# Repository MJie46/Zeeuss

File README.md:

# Zeeuss
>

#### IP5306+MP2045,电池充放电管理和升压输出
#### 背面引出5v,3.3v,BATT,VBUS,GND

###2.0版本
#### 尺寸 2.5x14mm

###1.0版本
#### 尺寸 20x18mm

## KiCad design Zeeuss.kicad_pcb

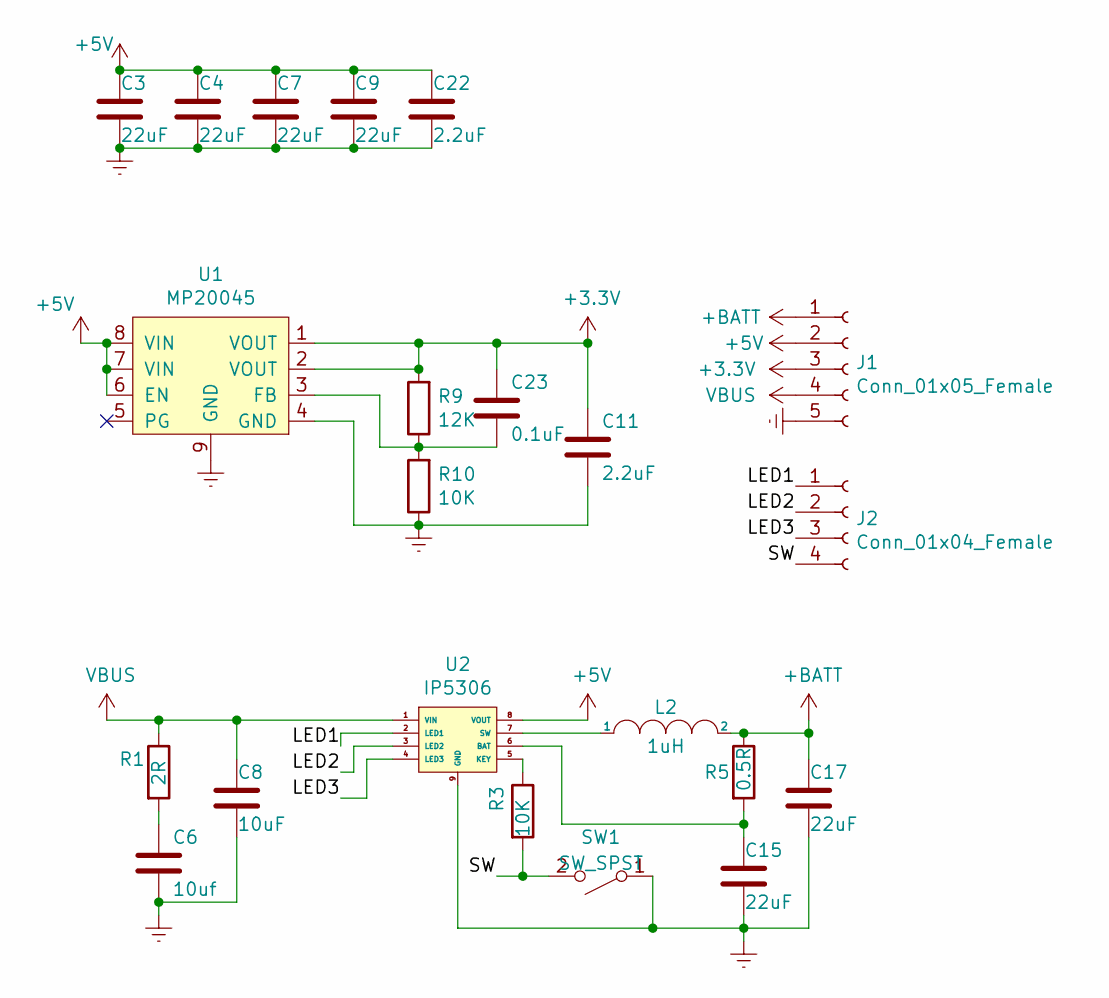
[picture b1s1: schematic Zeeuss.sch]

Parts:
C3, C4, C7, C9, C15, C17: 22uF; C_0603_1608Metric_Pad1.05x0.95mm_HandSolder
C6: 10uf; C_0603_1608Metric_Pad1.05x0.95mm_HandSolder
C8: 10uF; C_0603_1608Metric_Pad1.05x0.95mm_HandSolder
C11, C22: 2.2uF; C_0603_1608Metric_Pad1.05x0.95mm_HandSolder
C23: 0.1uF; C_0603_1608Metric_Pad1.05x0.95mm_HandSolder
J1: Conn_01x05_Female; PinHeader_1x05_P2.00mm_Vertical
J2: Conn_01x04_Female; PinHeader_1x04_P2.00mm_Vertical
L2: 1uH; L_Wuerth_HCI-7030
R1: 2R; R_0603_1608Metric_Pad1.05x0.95mm_HandSolder
R3, R10: 10K; R_0603_1608Metric_Pad1.05x0.95mm_HandSolder
R5: 0.5R; R_0603_1608Metric_Pad1.05x0.95mm_HandSolder
R9: 12K; R_0603_1608Metric_Pad1.05x0.95mm_HandSolder
SW1: SW_SPST; SW_SPST_B3U-1000P
U1: MP20045; SOIC-8-1EP_3.9x4.9mm_P1.27mm_EP2.41x3.3mm
U2: IP5306; SOIC-8-1EP_3.9x4.9mm_P1.27mm_EP2.29x3mm

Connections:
+3V3: C11.1, C23.1, J1.3, R9.2, U1.1 (VOUT), U1.2 (VOUT)
+5V: C3.1, C4.1, C7.1, C9.1, C22.1, J1.2, U1.6 (EN), U1.7 (VIN), U1.8 (VIN), U2.8 (VOUT)
+BATT: C17.1, J1.1, L2.2, R5.1
/LED1: J2.1, U2.2 (LED1)
/LED2: J2.2, U2.3 (LED2)
/LED3: J2.3, U2.4 (LED3)
/SW: J2.4, R3.2, SW1.2 (B)
Earth: C3.2, C4.2, C6.2, C7.2, C8.2, C9.2, C11.2, C15.2, C17.2, C22.2, J1.5, R10.1, SW1.1 (A), U1.4 (GND), U1.9 (GND), U2.9 (GND)
unnamed: C6.1, R1.2
unnamed: C15.1, R5.2, U2.6 (BAT)
unnamed: C23.2, R9.1, R10.2, U1.3 (FB)
unnamed: L2.1, U2.7 (SW)
unnamed: R3.1, U2.5 (KEY)
VBUS: C8.1, J1.4, R1.1, U2.1 (VIN)

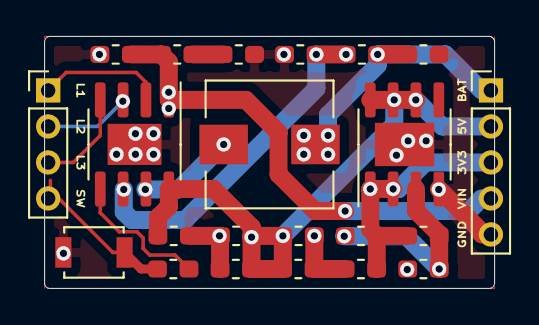
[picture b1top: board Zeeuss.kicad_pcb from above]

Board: 2 copper layers, 25.0 x 14.0 mm, 22 parts (0 on the bottom side), 14 nets.

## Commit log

2020-11-02 增加README,PCB图片
2020-11-10 更新图片
2021-03-12 2.0版本，删掉一些滤波电容，引出充电led引脚，取消自带led，引出开关，利用单片机控制开关，PCB重新布局
2021-03-22 更新文档，gerber
